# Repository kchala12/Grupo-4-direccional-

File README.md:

# Grupo-4-direccional

> **Robot Móvil Autónomo para Transporte Inteligente de Materiales**  
> Proyecto — Ingeniería Mecatrónica · Universidad Tecnológica de Pereira · 2026

---

## Descripción

Diseño y desarrollo de un **Vehículo Guiado Autónomo (AGV)** con visión artificial, capaz de transportar y descargar una carga de hasta **1 kg** a través de tres estaciones predefinidas, simulando operaciones logísticas en entornos industriales controlados.

El sistema utiliza **códigos QR** como referencias de navegación y una cámara **IMX219** para su detección en tiempo real, todo procesado sobre una **Raspberry Pi 5**.

---

## Objetivo

Desarrollar un robot funcional que complete de forma autónoma un ciclo de recolección y distribución de carga hacia tres estaciones destino con traccion diferencial, **sin intervención humana**, en un plazo de **16 semanas**.

---

##  Estructura del Repositorio

```
Grupo-4-direccional/
│
├── Documentacion/       # Matriz de documentos, informes y entregables
├── Electronica/         # Esquemas eléctricos, PCBs y firmware
├── Mecanica/            # Diseños CAD, planos y ensamblajes
├── src/                 # Código fuente principal (visión, navegación, control)
├── .gitignore
├── LICENSE
└── README.md
```
### 📁 [Documentacion](https://github.com/kchala12/Grupo-4-direccional-/tree/main/Documentacíon)
Contiene toda la documentación formal del proyecto: matriz de documentos, cronogramas, actas de reunión, informes de avance semanales y el informe final. También incluye presentaciones y entregables académicos requeridos por la universidad.
 
### 📁 [Electronica](https://github.com/kchala12/Grupo-4-direccional-/tree/main/Electronica)
Aquí se encuentran los esquemas eléctricos del sistema, diagramas de conexión de los componentes, diseños de PCB, selección y hoja de datos de los actuadores y drivers utilizados. También incluye el firmware de los microcontroladores encargados del control de motores y señales de los sensores.
 
### 📁 [Mecanica](https://github.com/kchala12/Grupo-4-direccional-/tree/main/Mecanica)
Contiene los diseños CAD del chasis del robot, planos técnicos de las piezas fabricadas o impresas en 3D, ensamblajes del sistema de tracción, soporte de carga y montaje de la cámara. 
 
### 📁 [src](https://github.com/kchala12/Grupo-4-direccional-/tree/main/src)
Código fuente principal del sistema autónomo. Incluye los módulos de visión artificial para la detección de códigos QR, algoritmos de navegación y control de trayectoria, lógica de gestión de estaciones y comunicación entre subsistemas. Todo desarrollado en Python sobre Raspberry Pi 5.
---

## 👥 Equipo

**Investigadores**
- Mateo Tabares Gil
- Federico Gómez Lotero
- Juan Sebastián Flórez Molina
- Kevin Andrés Chala González

**Director**
- Osiel Arbeláez Salazar

**Asesores**
- Angie Tatiana Rengifo Oviedo
- Carlos Andrés Rodríguez Pérez
- Edward Andrés González Ríos

---

## 🏛️ Institución

**Universidad Tecnológica de Pereira — Facultad de Tecnología — Febrero 2026**

---

## 📄 Licencia

Este proyecto está bajo la licencia especificada en el archivo [LICENSE](./LICENSE).

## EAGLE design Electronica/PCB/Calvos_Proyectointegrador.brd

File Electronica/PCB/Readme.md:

Estructura y diseño por fusion de la PCB usada en el proyecto

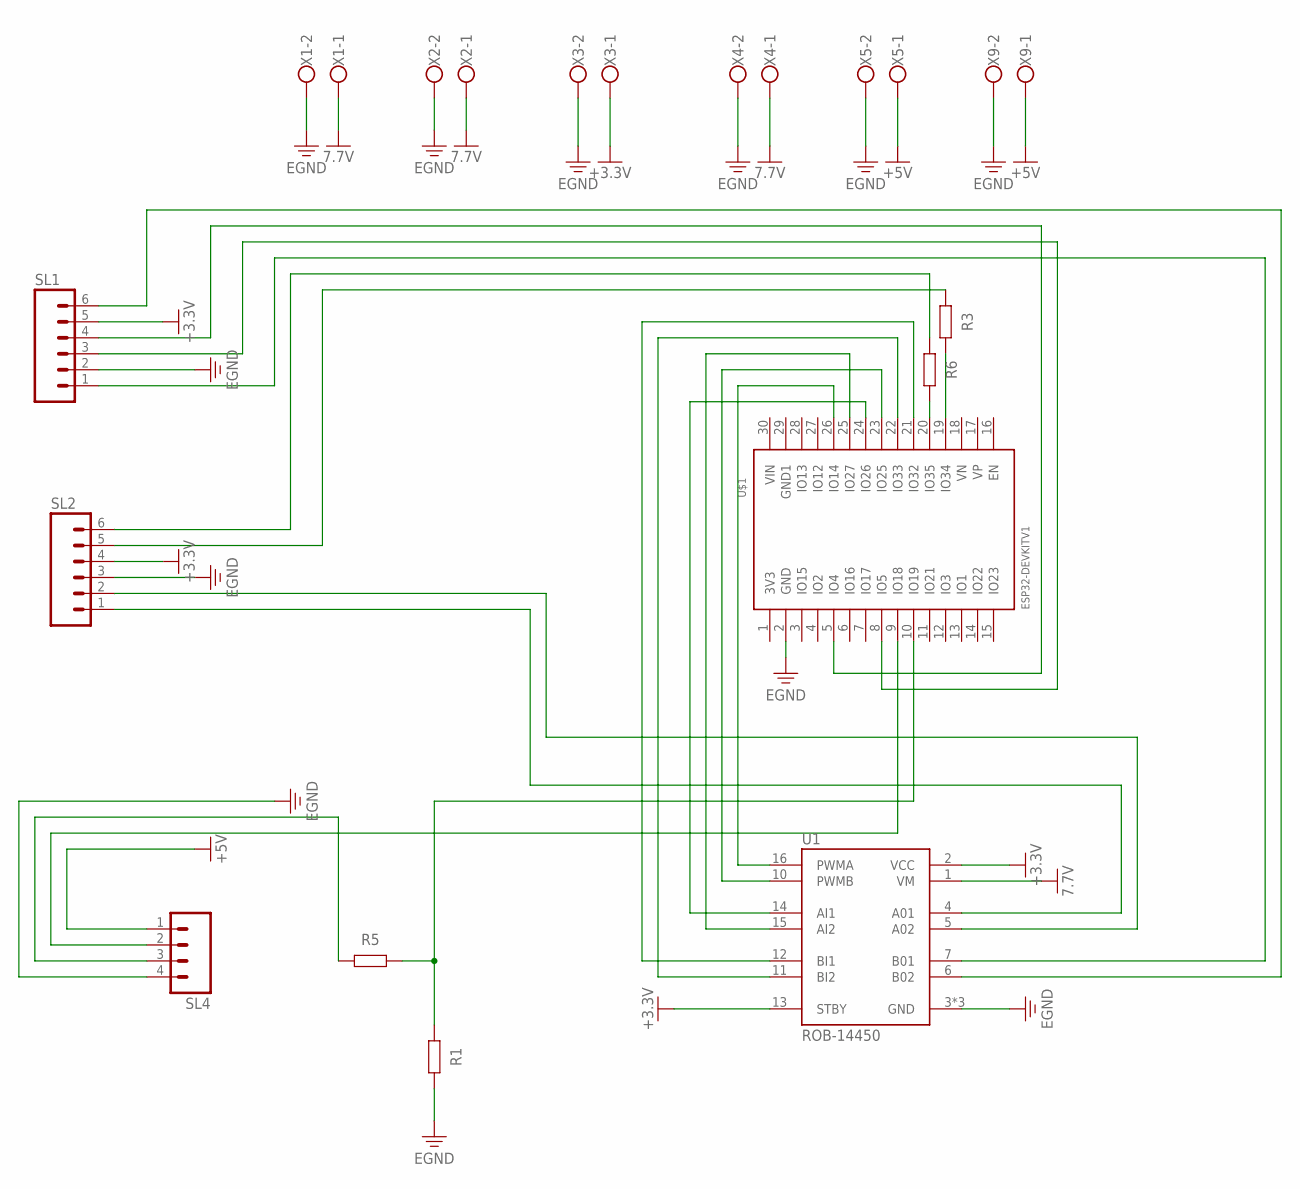
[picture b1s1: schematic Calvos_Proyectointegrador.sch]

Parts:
R1, R3, R5, R6: R_AXIAL-7.2MM-PITCH; RESAD724W46L381D178B
SL1, SL2: M06; 06P
SL4: M04; 04P
U1: ROB-14450; MODULE_ROB-14450
U$1: ESP32DEVKITV1; ESP32-DEVKITV1
X1, X2, X3, X4, X5, X9: W237-102

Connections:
7.7V: U1.1 (VM), X1.1, X2.1, X4.1
+3.3V: SL1.5, SL2.4, U1.2 (VCC), U1.13 (STBY), X3.1
+5V: SL4.1, X5.1, X9.1
EGND: R1.2, SL1.2, SL2.3, SL4.4, U1.3 (GND), U1.8 (GND), U1.9 (GND), U$1.2 (GND), X1.2, X2.2, X3.2, X4.2, X5.2, X9.2
unnamed: SL1.6, U1.6 (B02)
unnamed: U1.16 (PWMA), U$1.26 (IO14)
unnamed: U1.10 (PWMB), U$1.23 (IO25)
unnamed: U1.15 (AI2), U$1.25 (IO27)
unnamed: U1.14 (AI1), U$1.24 (IO26)
unnamed: U1.12 (BI1), U$1.21 (IO32)
unnamed: U1.11 (BI2), U$1.22 (IO33)
unnamed: SL1.4, U$1.5 (IO4)
unnamed: SL1.3, U$1.8 (IO5)
unnamed: SL1.1, U1.7 (B01)
unnamed: R6.1, SL2.6
unnamed: R3.1, SL2.5
unnamed: SL2.2, U1.5 (A02)
unnamed: SL2.1, U1.4 (A01)
unnamed: SL4.2, U$1.9 (IO18)
unnamed: R1.1, R5.2, U$1.10 (IO19)
unnamed: R5.1, SL4.3
unnamed: R6.2, U$1.20 (IO35)
unnamed: R3.2, U$1.19 (IO34)

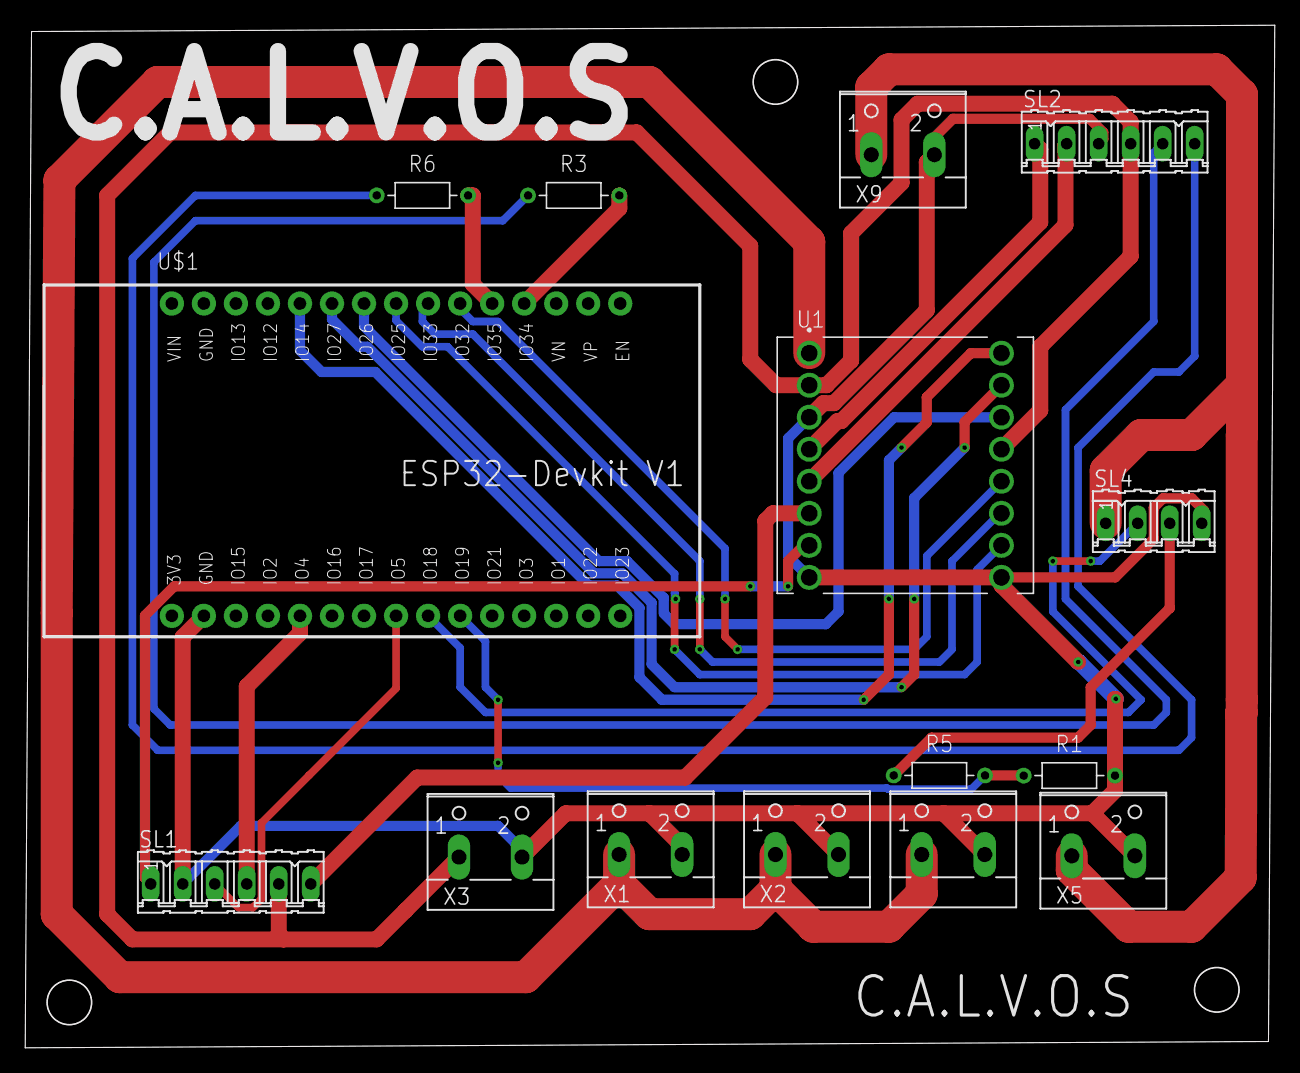
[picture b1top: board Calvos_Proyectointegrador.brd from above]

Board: 2 copper layers, 99.0 x 81.0 mm, 15 parts (0 on the bottom side), 23 nets.

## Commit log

2026-02-23 Creacion de carpetas de mecanica documentacion y codigo
2026-03-04 Imagenes de Prueba semana 4 y 5
2026-03-05 codigo de prueba para motores
2026-03-06 Delete src/controles_motores.py
    Eliminación código incorrecto
2026-03-06 segundo codigo de prubas para motor
2026-03-11 Prueba motores 3.1
2026-03-11 partes mecanicas del robot
2026-03-13 prueba de motores 4
2026-03-16 prueba motores #5
2026-03-17 programacion camara imx-219
2026-03-17 yolo programacion
2026-03-20 control de motores 6
2026-03-20 qr lector
2026-03-20 control de motores 7
2026-03-21 Subida de pruebas bitácora semana 6 y 7
2026-03-21 Delete Documentacíon/Circuito luego de la prueba de autonomia.jpeg
    Imagen equivocada
2026-03-21 corrección de la imagen anterior
2026-03-21 Dibujo CAD
2026-03-25 bitácoras actualizadas
2026-03-25 Cronograma del sistema
2026-03-25 camara y diseños cad
2026-03-25 Informe de Actividades
2026-03-25 Create Bitacoras
    Bitacoras
2026-03-25 README.md
2026-03-25 bITACORAS E INFORME
2026-03-25 Informe de Avance del GRUPO
2026-03-26 documentacion completa mecanica
2026-03-26 organización de pruebas
2026-03-27 8vo control de motores
2026-03-28 Imágenes de errores sucedidos
2026-03-28 Delete Documentacíon/Circuito luego de la prueba.jpeg
    Eliminado debido a q esta mal puesto
2026-03-28 Delete Documentacíon/Electronica.jpeg
    Eliminado debido a q esta mal puesto
2026-03-28 Delete Documentacíon/Puente H defectuoso.jpeg
    Eliminado debido a q esta mal puesto
2026-03-28 Delete Documentacíon/Reemplazo del circuito.jpeg
    Eliminado debido a que esta mal puesto
2026-03-28 Delete Documentacíon/base.jpeg
    Eliminado debido a que esta mal puesto
2026-03-28 Delete Documentacíon/motor defectuoso.jpeg
    Eliminado debido a que esta mal puesto
2026-03-28 Delete Documentacíon/motor funcional.mp4
    Eliminado debido a que esta mal puesto
2026-03-28 camara lista
2026-03-28 organizacion de archivos
2026-03-28 borrar un archivo
2026-03-30 actualizacion dibujo carro
2026-04-07 noveno control de motores
2026-04-09 decimo control de motores
2026-04-10 11vo control de motores
2026-04-10 doceavo control de motores
2026-04-14 Delete Documentacíon/Bitacoras/Bitacora Semana 8 y 9.docx
    Se Elimina la versión con solo el planeado y se reemplaza por la versión con ejecución.
2026-04-14 Añadir bitácoras
    Se añaden las bitácoras de las semanas 8 y 9 y el proyectado de las semanas 10 y 11
2026-04-16 nueva version de motores y camara
2026-04-16 actualizacion parte de mecanica
2026-04-16 codigo camara
2026-04-16 prueba obstaculos camara
2026-04-16 pruebas librerias 2
2026-04-16 segunda prueba librerias
2026-04-17 Create Readme.md
    Creacion de una nueva carpeta
2026-04-18 Delete Mecanica/Imágenes Electrónica/imagen_2026-04-17_203806201.png
    Imagen Equivocada
2026-04-20 prubas lunes #1
2026-04-24 actualizacion a bibliotecas
2026-04-24 codigo de calibracion
2026-04-24 actualizaciones por motor nuevo
2026-04-24 actualizacion de deteccion de lineas camara
2026-04-24 fix a la deteccion de obstaculos y lineas
2026-04-24 correciones a deteccion 2
2026-04-24 tercer ajuste
2026-04-30 cambio en la detección de obstaculos
2026-04-30 segundo ajuste de deteccion de obstaculos
2026-05-01 cambio a zona de deteccion de obstaculos
2026-05-01 cambios a la deteccion de obstaculos y fondo
2026-05-01 rapido
2026-05-01 nuevo objetos
2026-05-01 Actualizaciones Semana 13 y 14
2026-05-01 Encoders
2026-05-05 cambio de hsv a rgb
2026-05-05 correccion de cambio a rgb
2026-05-07 actualizacion
2026-05-11 revision
2026-05-12 deteccion de qr
2026-05-12 correccion obstaculos +qr
2026-05-12 dibujos con cotas
2026-05-12 actualizacion acciones con qr
2026-05-12 Update README.md
    Acctualización
2026-05-12 Update README.md
    Actualización 2
2026-05-12 primera calibracion para descarga 1
2026-05-12 Update README.md
    Actualización de títulos
2026-05-13 actualizacion de acciones en base a qr
2026-05-13 Add files via upload
    Avance del Poster del Proyecto.
2026-05-15 mecanica lista
2026-05-16 actualizacion de deteccion de curva
2026-05-18 Delete Documentacíon/Manual de Usuario/Manual de usuario IEEE.docx
    Rememplazo a pdf
2026-05-18 Add files via upload
    PDF leible
2026-05-19 Ultima semana
2026-05-20 Update README.md
    Actualización
2026-05-20 re organizacion de documentos
2026-05-20 Subida de material
2026-05-20 Delete Documentacíon/Poster_AGV_Robot (1).pptx.png
    Se subió la versión final en otra carpeta
2026-05-20 Articulo Publicable
2026-05-21 Delete Documentacíon/Presentaciones/JUNIO 2026 (2).pdf
    Errores de presentación
2026-05-21 Add files via upload
    Archivo Final
2026-05-21 Informe final
2026-05-21 Matriz de documentos
2026-05-22 nuevo bucle y sistema de carga
2026-05-22 fix1
2026-05-23 fix 1 hoy
2026-05-25 actualizacion diseño carro
2026-05-25 fix obstaculos durante acciones, deleted Herobrine
2026-05-26 Delete Electronica/PCB/C.A.L.V.O.S.zip
    Cambio a archivos buenos
2026-05-26 Add files via upload
    Archivos de texto .gbr para diseño pcb
2026-05-26 actualizacion de puntos de descarga
2026-05-28 added some bugs
2026-05-29 pls give us a 5 in the final if u reading this
2026-05-29 actualizacion menor
2026-05-29 cambio de ultrasonico a pines de raspberry, im really fkn tired of writing ts
2026-05-30 nueva parte de la carga
2026-05-30 Zona de descarga defectuosa
2026-05-30 Estetica nueva del robot
2026-05-30 Ejecución 16 y 17
2026-05-30 nuevo diseño
2026-05-30 actualizacion general
2026-05-30 adicion de IR a deteccion de estaciones
2026-06-02 nueva pared ultra
2026-06-03 actualizacion de emergencia
2026-06-03 actualizacion mm
2026-06-05 ultima actualizacion
